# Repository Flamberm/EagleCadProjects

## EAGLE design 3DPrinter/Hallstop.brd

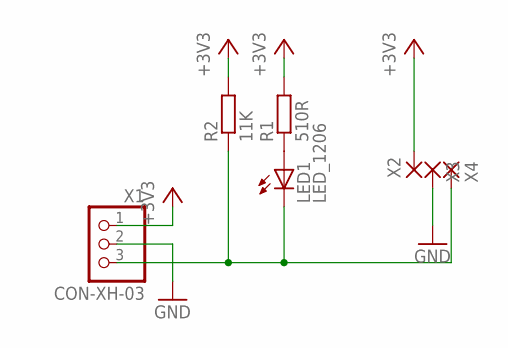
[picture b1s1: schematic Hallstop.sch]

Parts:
LED1: LED_1206; LED1206
R1: 510R; R0805
R2: 11K; R0805
X1: CON-XH-03; XH-03
X2, X3, X4: WIREPAD-SMD2; PAD-1.27X2.54

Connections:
+3V3: R1.2, R2.2, X1.1, X2.P$1
GND: X1.2, X3.P$1
unnamed: LED1.A, R1.1
unnamed: LED1.C, R2.1, X1.3, X4.P$1

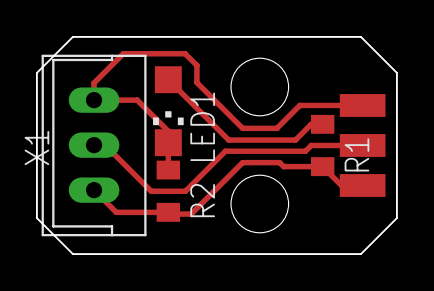
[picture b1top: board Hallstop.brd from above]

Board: 2 copper layers, 20.0 x 12.1 mm, 7 parts (0 on the bottom side), 4 nets.

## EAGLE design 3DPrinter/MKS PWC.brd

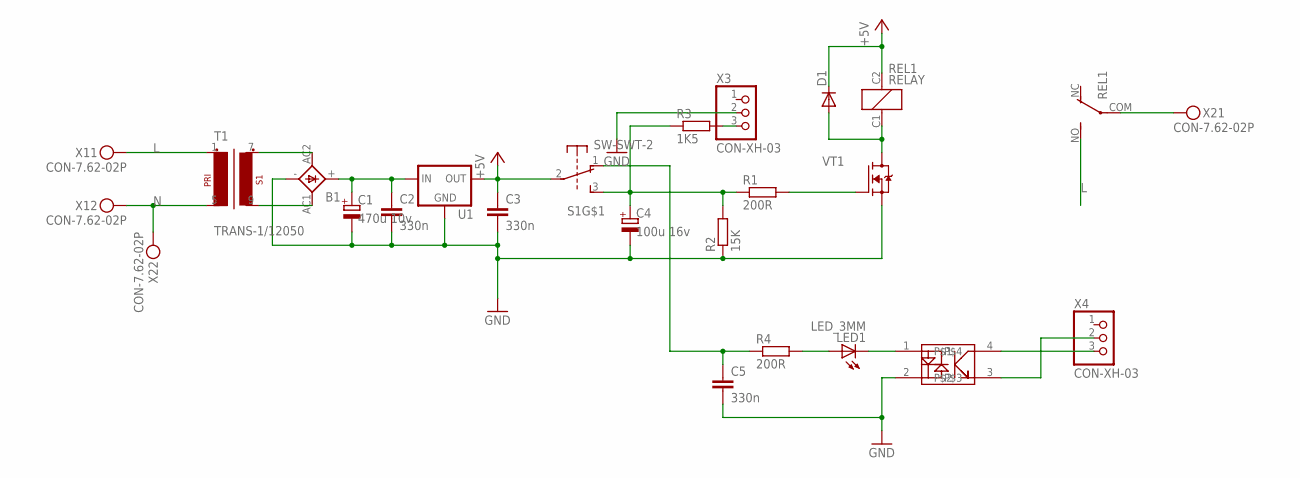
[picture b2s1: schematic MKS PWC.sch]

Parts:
B1: BRIDGEDBS; DBS
C1: 470u 10v; E2,5-7
C2, C3, C5: 330n; CAP1206
C4: 100u 16v; E2,5-7
D1: DIODE_ES1J; DO214AC
LED1: LED_3MM; LED3MM
R1, R4: 200R; RESC2012X50
R2: 15K; RESC2012X50
R3: 1K5; RESC2012X50
REL1: RELAY; RELAY-15X18
S1: SW-SWT-2; SWT-2
T1: TRANS-1/12050; 32.5-27.5-30
U1: V-REGDPAK; DPAK
U$1: OPTO-EL3H4(TA)-VG; SSOP4
VT1: FET-NPF-2X2; POWERFLAT-2X2
X1, X2: CON-7.62-02P; KF25C-7.62-02P-13
X3, X4: CON-XH-03; XH-03

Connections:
+5V: C3.1, D1.C, REL1.C2, S1.2, U1.3 (OUT)
GND: B1.-, C1.-, C2.2, C3.2, C4.-, C5.2, R2.1, U1.2(PAD) (GND), U$1.2, VT1.S, VT1.S4 (S), X3.2
L: REL1.NO, T1.1 (P1-1), X1.P$1
N: T1.5 (P1-2), X1.P$2, X2.P$2
unnamed: B1.AC2, T1.7 (S1-1)
unnamed: B1.AC1, T1.9 (S1-2)
unnamed: C4.+, R1.1, R2.2, R3.1, S1.3
unnamed: B1.+, C1.+, C2.1, U1.1 (IN)
unnamed: D1.A, REL1.C1, VT1.D, VT1.D1 (D), VT1.D2 (D), VT1.D5 (D), VT1.D6 (D)
unnamed: R1.2, VT1.G3 (G)
unnamed: REL1.COM, X2.P$1
unnamed: R3.2, X3.3
unnamed: C5.1, R4.1, S1.1
unnamed: LED1.K (C), U$1.1
unnamed: LED1.A, R4.2
unnamed: U$1.4, X4.3
unnamed: U$1.3, X4.2

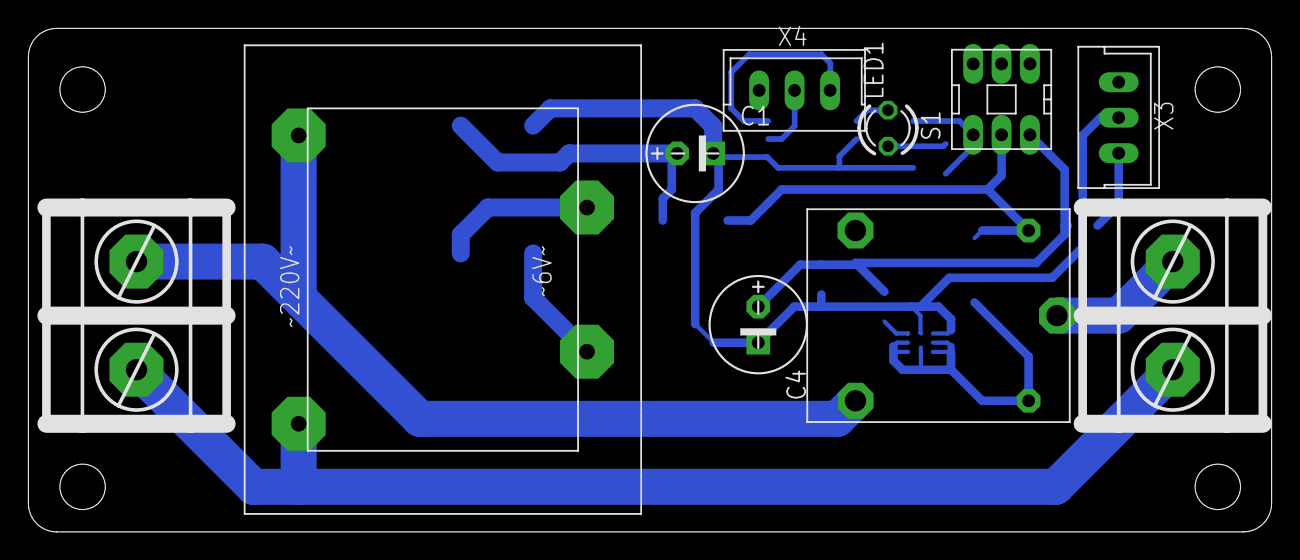
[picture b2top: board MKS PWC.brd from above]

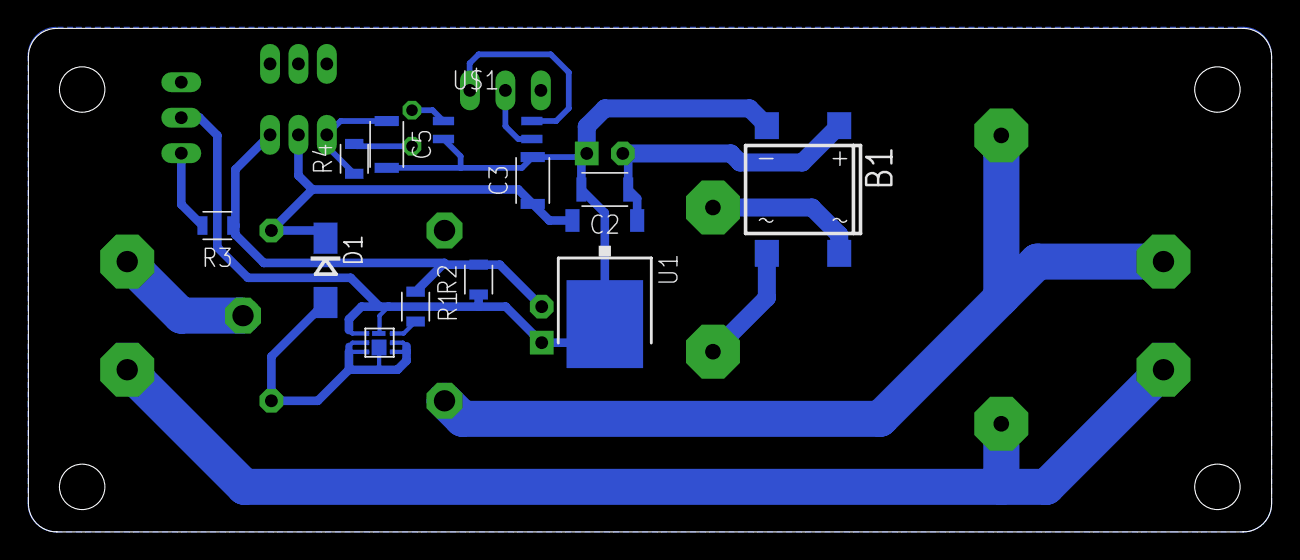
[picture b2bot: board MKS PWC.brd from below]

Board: 2 copper layers, 87.6 x 35.5 mm, 22 parts (12 on the bottom side), 17 nets.

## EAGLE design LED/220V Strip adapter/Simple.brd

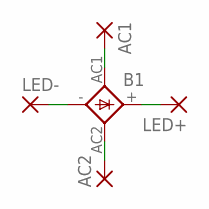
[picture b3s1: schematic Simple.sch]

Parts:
AC1, AC2: WIREPAD-SMD2; PAD-1.27X2.54
B1: BRIDGEDBS; DBS
LED+: WIREPAD-SMD2; PAD-1.27X2.54
LED-: WIREPAD-SMD2; PAD-1.27X2.54

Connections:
unnamed: B1.-, LED-.P$1
unnamed: AC1.P$1, B1.AC1
unnamed: B1.+, LED+.P$1
unnamed: AC2.P$1, B1.AC2

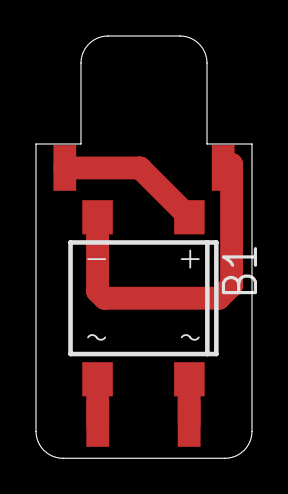
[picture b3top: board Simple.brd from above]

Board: 2 copper layers, 12.0 x 23.5 mm, 5 parts (0 on the bottom side), 4 nets.

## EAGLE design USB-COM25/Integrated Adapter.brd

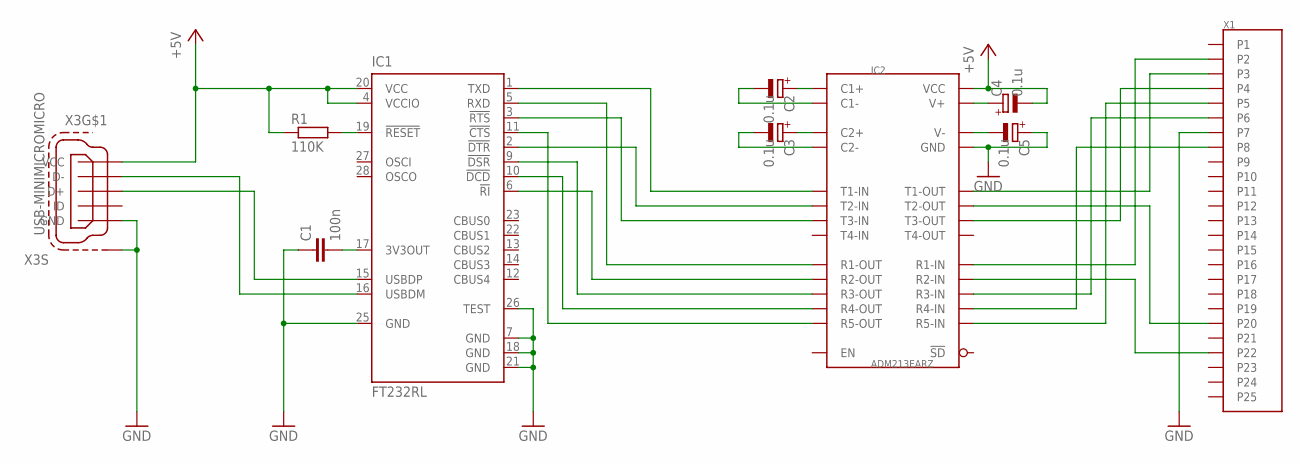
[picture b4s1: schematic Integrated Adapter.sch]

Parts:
C1: 100n; CAP0805
C2, C3, C4, C5: 0.1u; CAPMP3317X180
IC1: FT232RL; SSOP28
IC2: ADM213EARZ; SO28L
R1: 110K; RESC2012X50
X1: DP-25; DB-25F_SMD
X3: USB-MINIMICROMICRO; USB-B-MICRO-SMD

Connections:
+5V: C4.2 (-), IC1.4 (VCCIO), IC1.20 (VCC), IC2.11 (VCC), R1.1, X3.VBUS (VCC)
C1+: C2.1 (+), IC2.12 (C1+)
C1-: C2.2 (-), IC2.14 (C1-)
C2+: C3.1 (+), IC2.15 (C2+)
C2-: C3.2 (-), IC2.16 (C2-)
GND: C1.1, C5.1 (+), IC1.7 (GND), IC1.18 (GND), IC1.21 (GND), IC1.25 (GND), IC1.26 (TEST), IC2.10 (GND), X1.P7, X3.GND, X3.SHIELD1 (S1), X3.SHIELD2 (S1), X3.SHIELD3 (S1)
unnamed: C1.2, IC1.17 (3V3OUT)
unnamed: IC1.19 (!RESET), R1.2
unnamed: IC1.1 (TXD), IC2.7 (T1-IN)
unnamed: IC1.2 (!DTR), IC2.6 (T2-IN)
unnamed: IC1.3 (!RTS), IC2.20 (T3-IN)
unnamed: IC1.5 (RXD), IC2.8 (R1-OUT)
unnamed: IC1.6 (!RI), IC2.5 (R2-OUT)
unnamed: IC1.9 (!DSR), IC2.26 (R3-OUT)
unnamed: IC1.10 (!DCD), IC2.22 (R4-OUT)
unnamed: IC1.11 (!CTS), IC2.19 (R5-OUT)
unnamed: IC2.2 (T1-OUT), X1.P3
unnamed: IC2.9 (R1-IN), X1.P2
unnamed: IC2.1 (T3-OUT), X1.P4
unnamed: IC2.18 (R5-IN), X1.P5
unnamed: IC2.27 (R3-IN), X1.P6
unnamed: IC2.3 (T2-OUT), X1.P20
unnamed: IC2.4 (R2-IN), X1.P22
unnamed: IC2.23 (R4-IN), X1.P8
USB_N: IC1.16 (USBDM), X3.D-
USB_P: IC1.15 (USBDP), X3.D+
V+: C4.1 (+), IC2.13 (V+)
V-: C5.2 (-), IC2.17 (V-)

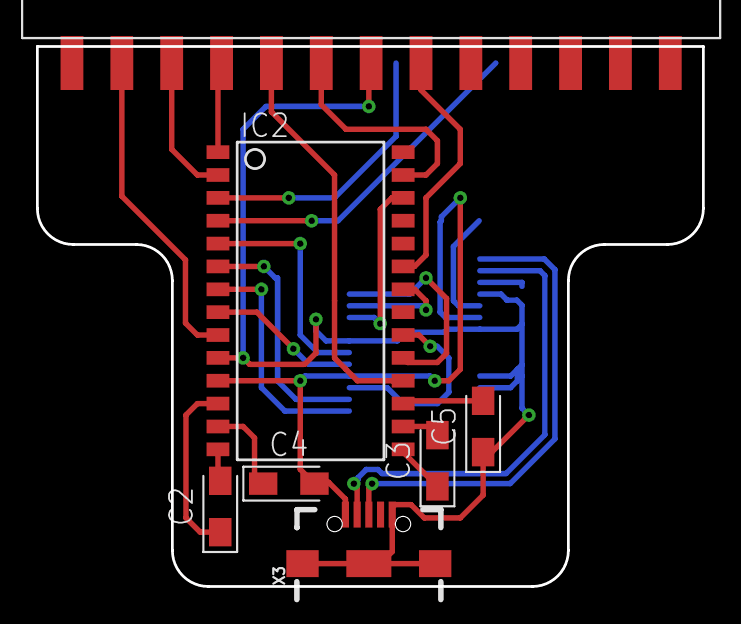
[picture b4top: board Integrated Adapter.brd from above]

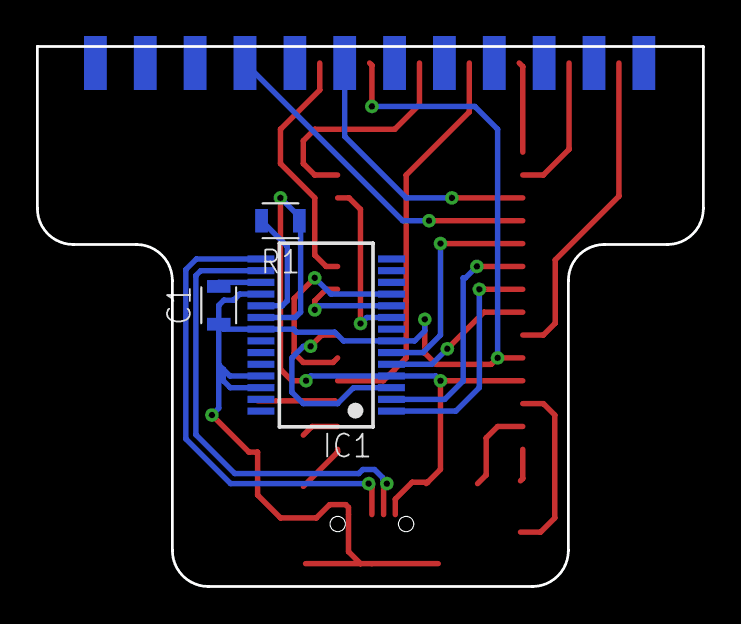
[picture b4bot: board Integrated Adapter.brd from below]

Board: 2 copper layers, 37.0 x 30.0 mm, 10 parts (3 on the bottom side), 28 nets.

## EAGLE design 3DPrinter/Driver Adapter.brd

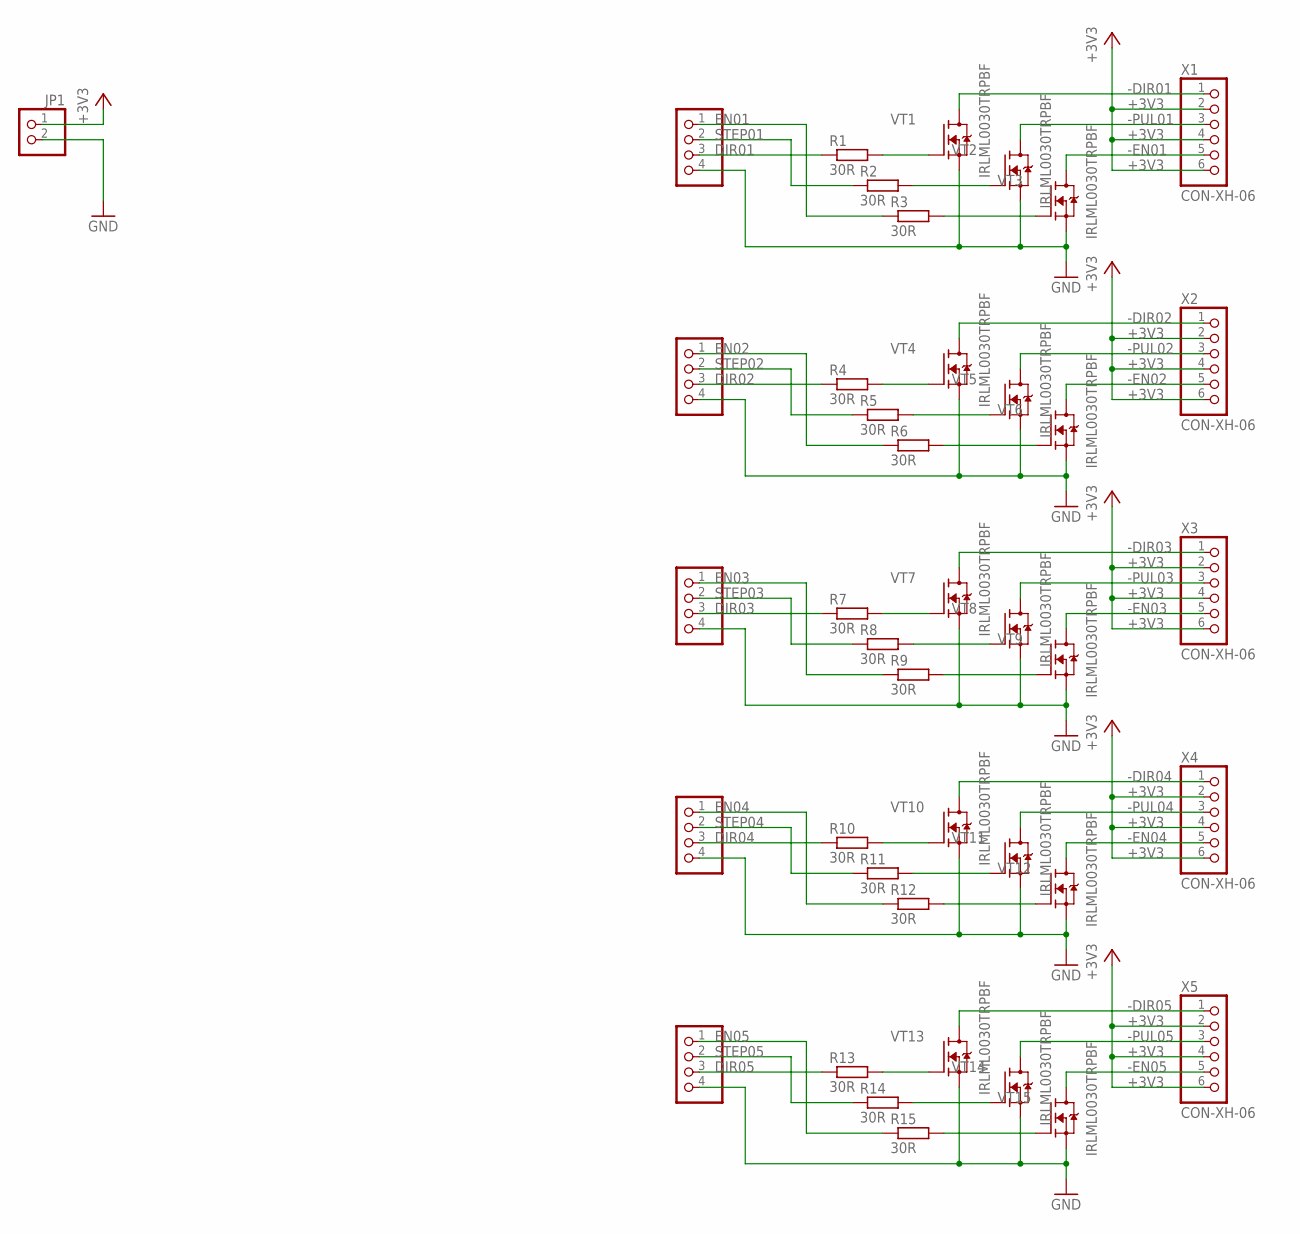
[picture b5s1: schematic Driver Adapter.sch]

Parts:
JP1: PINHD-1X2; 1X02
JP2, JP3, JP4, JP5, JP6: PINHD-1X4; 1X04
R1, R2, R3, R4, R5, R6, R7, R8, R9, R10, R11, R12, R13, R14, R15: 30R; RESC3216X60
VT1, VT2, VT3, VT4, VT5, VT6, VT7, VT8, VT9, VT10, VT11, VT12, VT13, VT14, VT15: IRLML0030TRPBF; SOT95P240X115-3
X1, X2, X3, X4, X5: CON-XH-06; XH-06

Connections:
+3V3: JP1.1, X1.2, X1.4, X1.6, X2.2, X2.4, X2.6, X3.2, X3.4, X3.6, X4.2, X4.4, X4.6, X5.2, X5.4, X5.6
-DIR01: VT1.3 (D), X1.1
-DIR02: VT4.3 (D), X2.1
-DIR03: VT7.3 (D), X3.1
-DIR04: VT10.3 (D), X4.1
-DIR05: VT13.3 (D), X5.1
-EN01: VT3.3 (D), X1.5
-EN02: VT6.3 (D), X2.5
-EN03: VT9.3 (D), X3.5
-EN04: VT12.3 (D), X4.5
-EN05: VT15.3 (D), X5.5
-PUL01: VT2.3 (D), X1.3
-PUL02: VT5.3 (D), X2.3
-PUL03: VT8.3 (D), X3.3
-PUL04: VT11.3 (D), X4.3
-PUL05: VT14.3 (D), X5.3
DIR01: JP2.3, R1.1
DIR02: JP3.3, R4.1
DIR03: JP4.3, R7.1
DIR04: JP5.3, R10.1
DIR05: JP6.3, R13.1
EN01: JP2.1, R3.1
EN02: JP3.1, R6.1
EN03: JP4.1, R9.1
EN04: JP5.1, R12.1
EN05: JP6.1, R15.1
GND: JP1.2, JP2.4, JP3.4, JP4.4, JP5.4, JP6.4, VT1.2 (S), VT2.2 (S), VT3.2 (S), VT4.2 (S), VT5.2 (S), VT6.2 (S), VT7.2 (S), VT8.2 (S), VT9.2 (S), VT10.2 (S), VT11.2 (S), VT12.2 (S), VT13.2 (S), VT14.2 (S), VT15.2 (S)
unnamed: R1.2, VT1.1 (G)
unnamed: R2.2, VT2.1 (G)
unnamed: R3.2, VT3.1 (G)
unnamed: R4.2, VT4.1 (G)
unnamed: R5.2, VT5.1 (G)
unnamed: R6.2, VT6.1 (G)
unnamed: R7.2, VT7.1 (G)
unnamed: R8.2, VT8.1 (G)
unnamed: R9.2, VT9.1 (G)
unnamed: R10.2, VT10.1 (G)
unnamed: R11.2, VT11.1 (G)
unnamed: R12.2, VT12.1 (G)
unnamed: R13.2, VT13.1 (G)
unnamed: R14.2, VT14.1 (G)
unnamed: R15.2, VT15.1 (G)
STEP01: JP2.2, R2.1
STEP02: JP3.2, R5.1
STEP03: JP4.2, R8.1
STEP04: JP5.2, R11.1
STEP05: JP6.2, R14.1

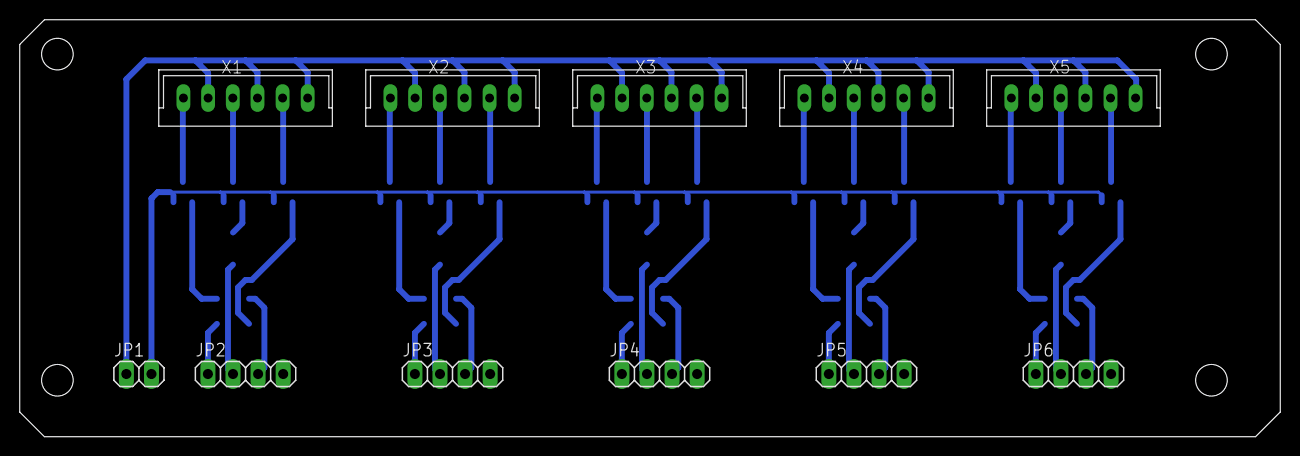
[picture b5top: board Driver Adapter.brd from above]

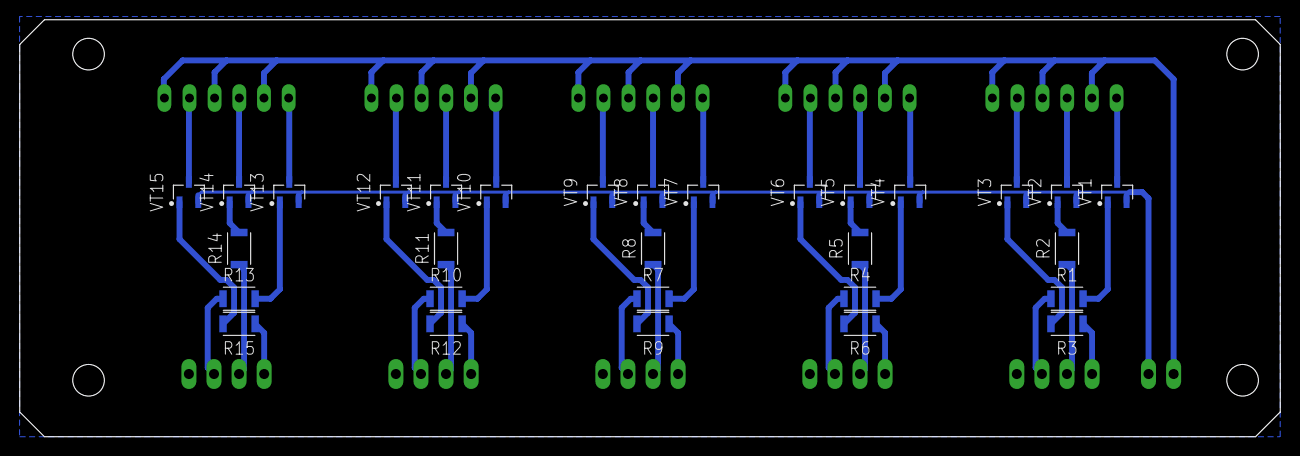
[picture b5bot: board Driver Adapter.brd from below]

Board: 2 copper layers, 127.6 x 42.2 mm, 41 parts (30 on the bottom side), 47 nets.

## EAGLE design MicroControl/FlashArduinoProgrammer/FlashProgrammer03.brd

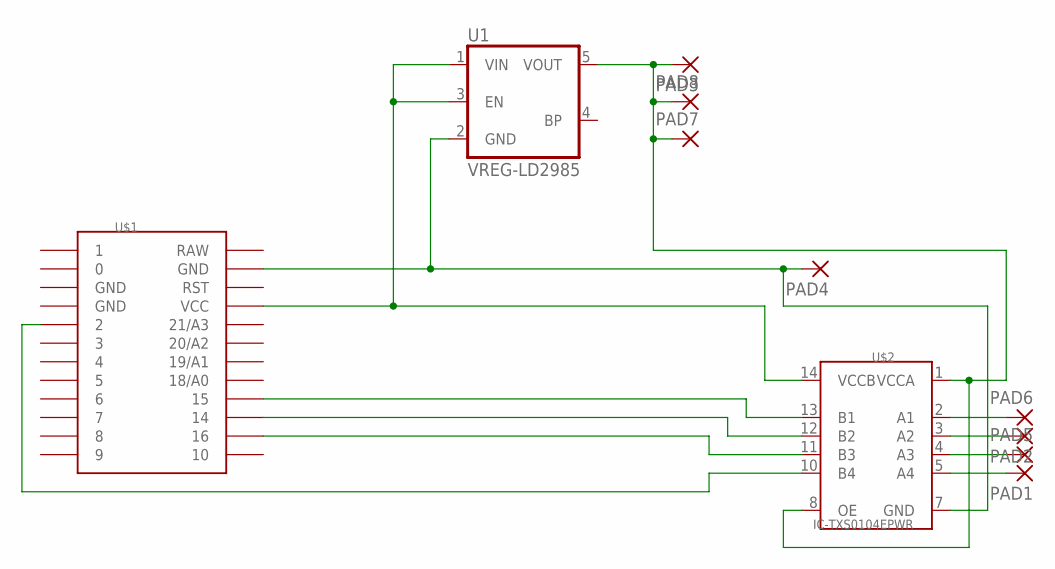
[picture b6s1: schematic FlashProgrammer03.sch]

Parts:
PAD1, PAD2, PAD3, PAD4, PAD5, PAD6, PAD7, PAD8: 1,6/0,8
U1: VREG-LD2985; SOT95P280X145-5
U$1: PROMICRO
U$2: IC-TXS0104EPWR; TSSOP14

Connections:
0: U$1.0
1: U$1.1
GND: U$1.GND@2 (GND)
unnamed: U$1.2, U$2.10 (B4)
unnamed: PAD4.1, U1.2 (GND), U$1.GND@1 (GND), U$2.7 (GND)
unnamed: U$1.15, U$2.13 (B1)
unnamed: PAD3.1, PAD7.1, PAD8.1, U1.5 (VOUT), U$2.1 (VCCA), U$2.8 (OE)
unnamed: U$1.14, U$2.12 (B2)
unnamed: U$1.16, U$2.11 (B3)
unnamed: U1.1 (VIN), U1.3 (EN), U$1.VCC, U$2.14 (VCCB)
unnamed: PAD6.1, U$2.2 (A1)
unnamed: PAD2.1, U$2.3 (A2)
unnamed: PAD5.1, U$2.4 (A3)
unnamed: PAD1.1, U$2.5 (A4)
RAW: U$1.RAW

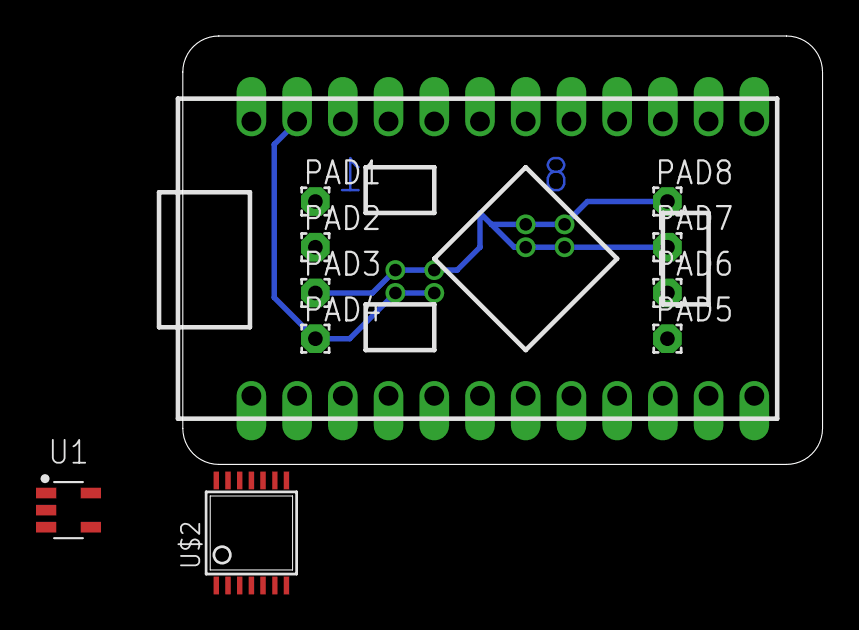
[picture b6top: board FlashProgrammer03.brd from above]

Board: 2 copper layers, 35.5 x 23.8 mm, 11 parts (0 on the bottom side), 11 nets.

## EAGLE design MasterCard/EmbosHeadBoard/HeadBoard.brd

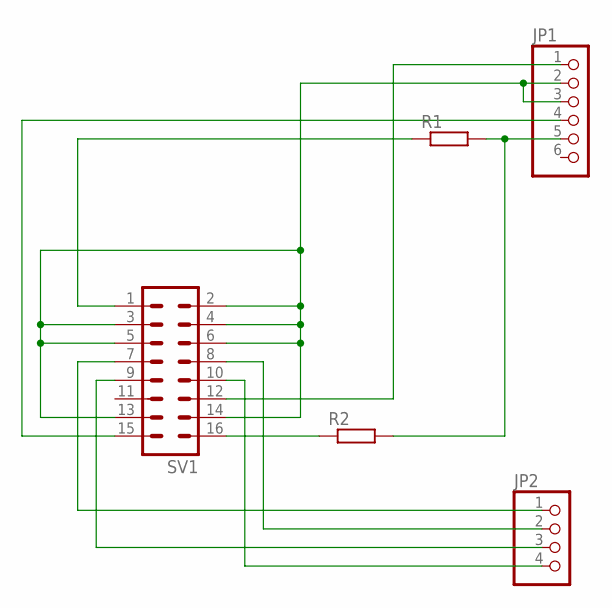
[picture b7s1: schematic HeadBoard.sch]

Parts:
JP1: PINHD-1X6; 1X06
JP2: PINHD-1X4; 1X04
R1, R2: R_R0805; RESC2012X50
SV1: ML16

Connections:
unnamed: JP2.1, SV1.7
unnamed: JP2.2, SV1.8
unnamed: JP2.3, SV1.9
unnamed: JP2.4, SV1.10
unnamed: JP1.1, SV1.12
unnamed: JP1.2, JP1.3, SV1.2, SV1.3, SV1.4, SV1.5, SV1.6, SV1.13, SV1.14
unnamed: JP1.4, SV1.15
unnamed: JP1.5, R1.2, R2.2
unnamed: R1.1, SV1.1
unnamed: R2.1, SV1.16

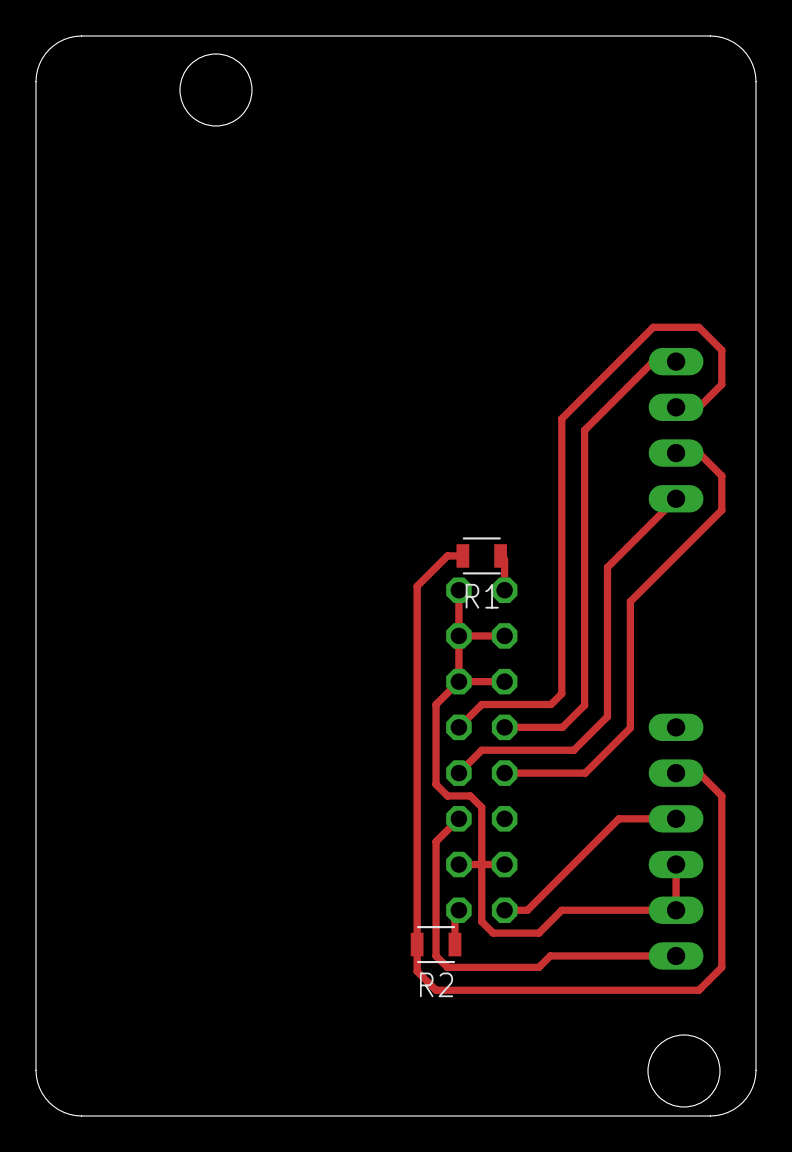
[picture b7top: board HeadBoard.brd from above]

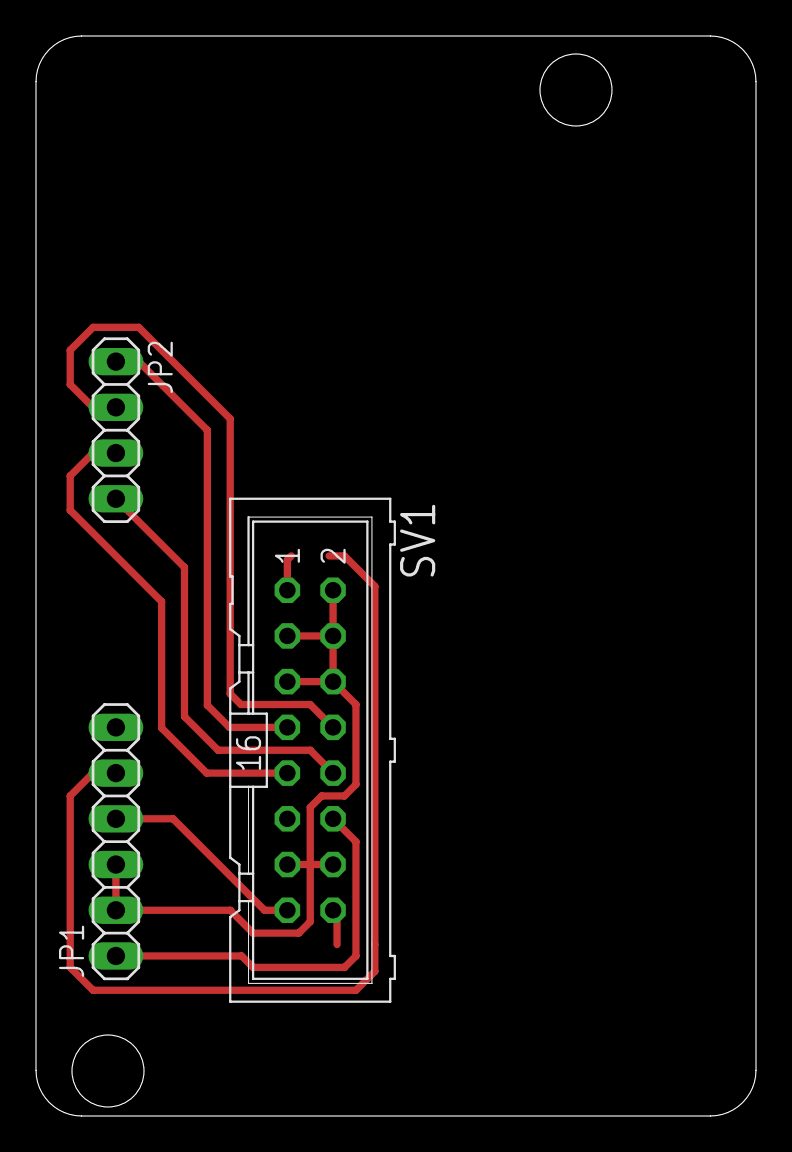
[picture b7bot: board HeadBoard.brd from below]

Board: 2 copper layers, 40.0 x 60.0 mm, 5 parts (3 on the bottom side), 10 nets.

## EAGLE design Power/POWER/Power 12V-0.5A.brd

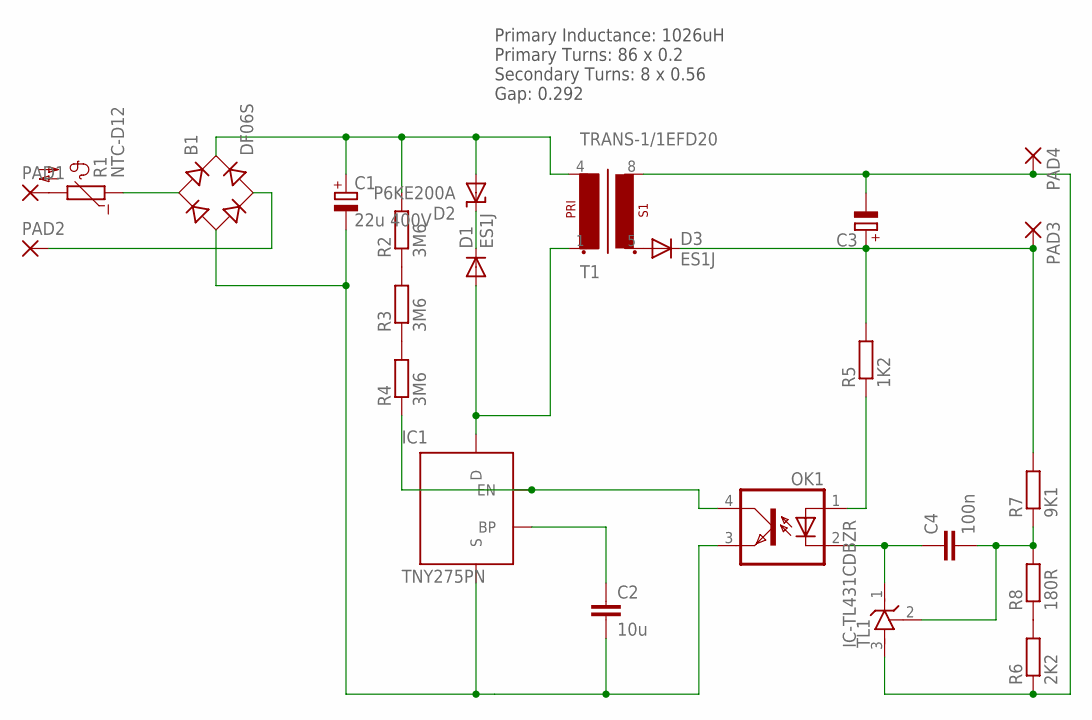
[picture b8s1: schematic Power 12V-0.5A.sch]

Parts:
B1: DF06S; DFS
C1: 22u 400V; E5-13
C2: 10u; C1210
C3: CPOL-EUE7.5-18; E7,5-18
C4: 100n; C0805
D1, D3: ES1J; DO214AC
D2: P6KE200A; DO15-12
IC1: TNY275PN; DIP-8C
OK1: OPTOTRANSPC817; DIL04
PAD1, PAD2, PAD3, PAD4: SMD5; SMD2,54-5,08
R1: NTC-D12
R2, R3, R4: 3M6; R0805
R5: 1K2; R1206
R6: 2K2; RESC2012X50
R7: 9K1; R1206
R8: 180R; R1206
T1: TRANS-1/1EFD20; EFD20_8PIN
TL1: IC-TL431CDBZR; SOT23

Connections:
unnamed: PAD1.1, R1.2
unnamed: B1.AC1, R1.1
unnamed: B1.AC2, PAD2.1
unnamed: B1.+, C1.+, D2.A, R2.2, T1.4 (P1-2)
unnamed: B1.-, C1.-, C2.2, IC1.5 (S), IC1.6 (S), IC1.7 (S), IC1.8 (S), OK1.3 (EMIT)
unnamed: R6.2, R8.1
unnamed: C2.1, IC1.2 (BP)
unnamed: D1.A, IC1.4 (D), T1.1 (P1-1)
unnamed: D1.C, D2.C
unnamed: IC1.1 (EN), OK1.4 (COL), R4.1
unnamed: R2.1, R3.2
unnamed: R3.1, R4.2
unnamed: D3.A, T1.5 (S1-1)
unnamed: C3.+, D3.C, PAD3.1, R5.2, R7.2
unnamed: C3.-, PAD4.1, R6.1, T1.8 (S1-2), TL1.3 (A)
unnamed: OK1.1 (A), R5.1
unnamed: C4.1, OK1.2 (C), TL1.1 (C)
unnamed: C4.2, R7.1, R8.2, TL1.2 (R)

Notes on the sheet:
Primary Inductance: 1026uH Primary Turns: 86 x 0.2 Secondary Turns: 8 x 0.56 Gap: 0.292
